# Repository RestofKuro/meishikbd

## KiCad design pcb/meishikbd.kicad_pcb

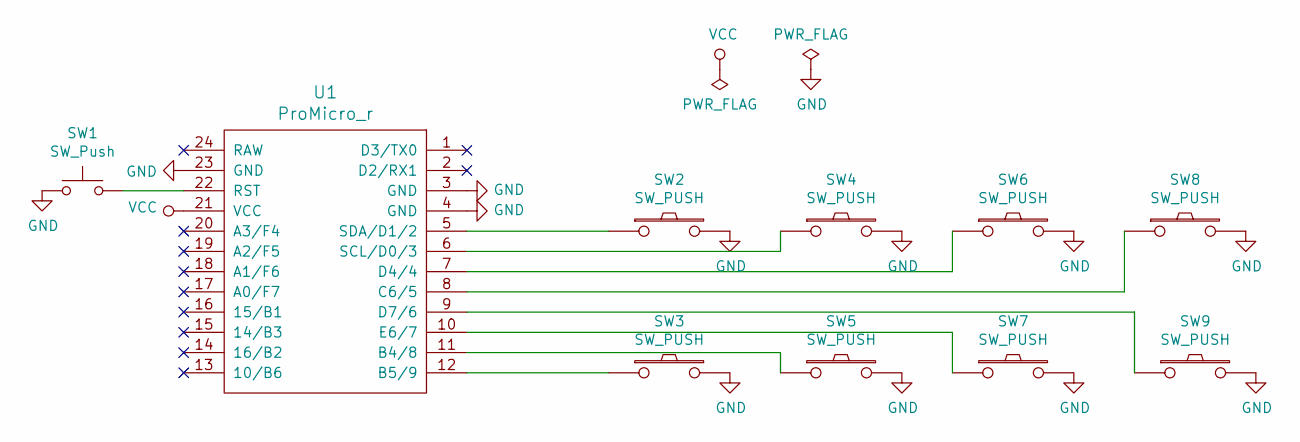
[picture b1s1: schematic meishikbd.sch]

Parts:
SW1: SW_Push; ResetSW
SW2, SW3, SW4, SW5, SW6, SW7, SW8, SW9: SW_PUSH; CherryMX_1u
U1: ProMicro_r; ProMicro_v3

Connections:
GND: SW1.1, SW2.2, SW3.2, SW4.2, SW5.2, SW6.2, SW7.2, SW8.2, SW9.2, U1.3 (GND), U1.4 (GND), U1.23 (GND)
unnamed: SW1.2, U1.22 (RST)
unnamed: SW2.1, U1.5 (SDA/D1/2)
unnamed: SW3.1, U1.12 (B5/9)
unnamed: SW4.1, U1.6 (SCL/D0/3)
unnamed: SW5.1, U1.11 (B4/8)
unnamed: SW6.1, U1.7 (D4/4)
unnamed: SW7.1, U1.10 (E6/7)
unnamed: SW8.1, U1.8 (C6/5)
unnamed: SW9.1, U1.9 (D7/6)
VCC: U1.21 (VCC)

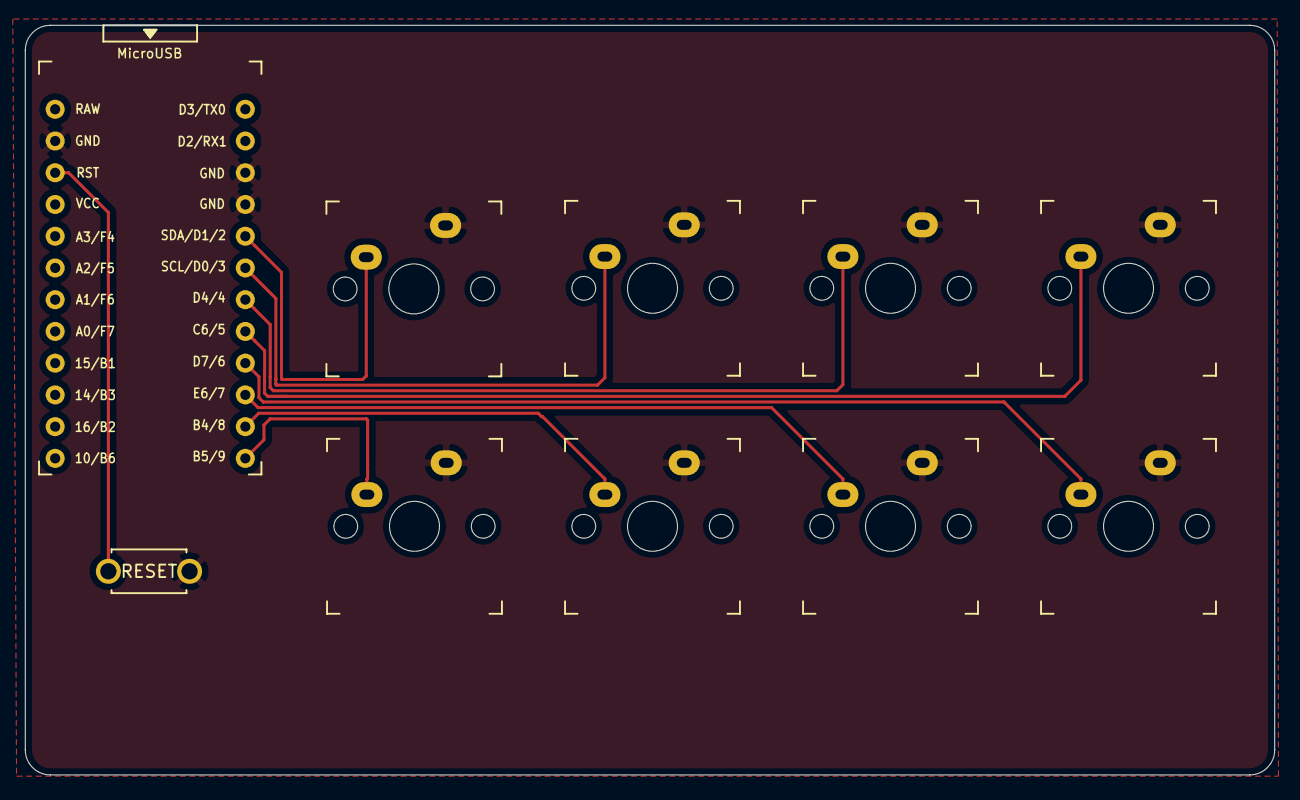
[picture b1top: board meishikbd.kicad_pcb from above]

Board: 2 copper layers, 100.0 x 60.0 mm, 10 parts (0 on the bottom side), 10 nets.

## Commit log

2019-05-01 first add
2019-05-01 add buildguide.md (jp)
2019-05-01 Update buildguide.md (jp)
2019-05-03 fix buildeguide
2019-06-04 add default.hex
2019-06-04 fix buildguide
